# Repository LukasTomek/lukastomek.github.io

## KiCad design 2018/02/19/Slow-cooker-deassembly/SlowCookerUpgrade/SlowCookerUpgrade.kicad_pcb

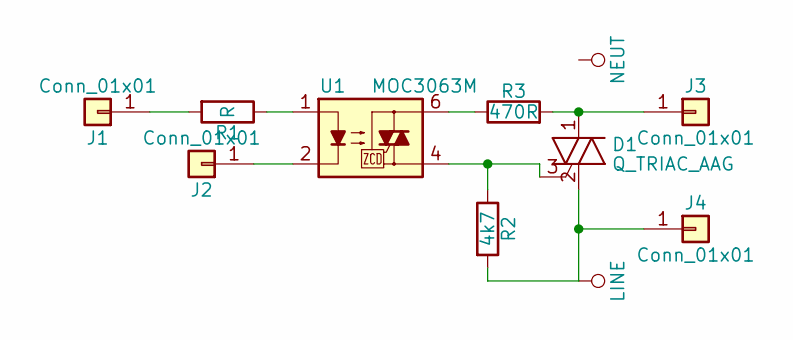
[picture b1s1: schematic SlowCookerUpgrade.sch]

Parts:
D1: Q_TRIAC_AAG; TO-220_Vertical
J1, J2, J3, J4: Conn_01x01; Pin_Header_Angled_1x01_Pitch2.00mm
R1: R; R_1206
R2: 4k7; R_1206
R3: 470R; R_1206
U1: MOC3063M; DIP-6_W7.62mm

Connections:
LINE: D1.2 (A2), J4.1, R2.2
unnamed: D1.1 (A1), J3.1, R3.2
unnamed: D1.3 (G), R2.1, U1.4
unnamed: J1.1, R1.2
unnamed: J2.1, U1.2
unnamed: R1.1, U1.1
unnamed: R3.1, U1.6

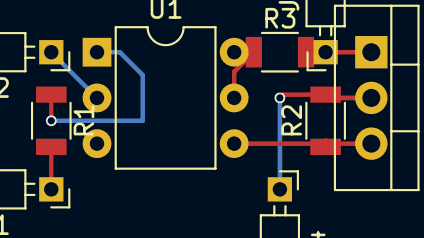
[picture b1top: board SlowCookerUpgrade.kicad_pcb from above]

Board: 2 copper layers, 9 parts (0 on the bottom side), 7 nets.

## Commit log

2019-07-16 Site updated: 2019-07-16 12:22:46
2019-07-16 Site updated: 2019-07-16 12:33:02
